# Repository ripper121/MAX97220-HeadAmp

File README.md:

# MAX97220-HeadAmp
HeadAmp-MAX97220A

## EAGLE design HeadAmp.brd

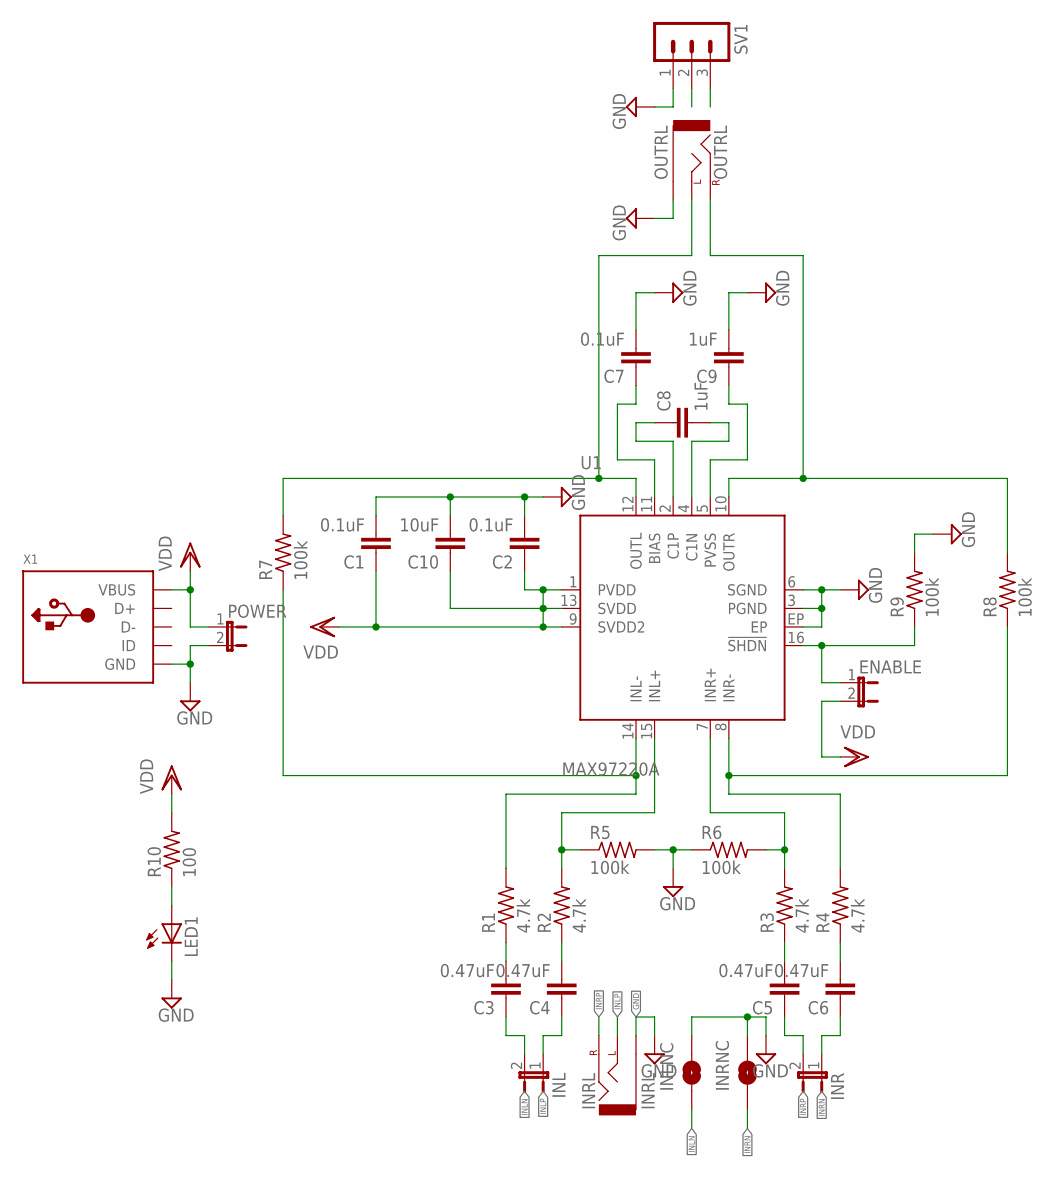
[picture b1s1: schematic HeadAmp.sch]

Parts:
C1, C2, C7: 0.1uF; C0603
C3, C4, C5, C6: 0.47uF; C0603
C8, C9: 1uF; C0603
C10: 10uF; C0603
ENABLE: JP1E; JP1
INL: JP1E; JP1
INLNC: SOLDERJUMPERNO; SJ_2S-NO
INR: JP1E; JP1
INRL: INRL; AUDIO-JACK-3.5MM-SMD
INRNC: SOLDERJUMPERNO; SJ_2S-NO
LED1: LEDCHIP-LED0805; CHIP-LED0805
OUTRL: OUTRL; AUDIO-JACK-3.5MM-SMD
POWER: JP1E; JP1
R1, R2, R3, R4: 4.7k; R0603
R5, R6, R7, R8, R9: 100k; R0603
R10: 100; R0603
SV1: MA03-1
U1: MAX97220A; TQFN16
X1: USB_MICRO_20329_V2; 4UCONN_20329_V2

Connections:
GND: C1.2, C2.2, C7.2, C9.2, C10.2, INLNC.2, INRL.5, INRNC.2, LED1.C, OUTRL.5, POWER.2, R5.2, R6.1, R9.2, SV1.1, U1.3 (PGND), U1.6 (SGND), U1.EP, X1.BASE@1 (GND), X1.BASE@2 (GND), X1.GND, X1.SPRT@1 (GND), X1.SPRT@2 (GND), X1.SPRT@3 (GND), X1.SPRT@4 (GND)
INLN: C3.1, INL.2, INLNC.1
INLP: C4.1, INL.1, INRL.4
INRN: C6.1, INR.1, INRNC.1
INRP: C5.1, INR.2, INRL.1
LOUT: OUTRL.4, R7.2, SV1.2, U1.12 (OUTL)
unnamed: C8.1, U1.2 (C1P)
unnamed: C8.2, U1.4 (C1N)
unnamed: C9.1, U1.5 (PVSS)
unnamed: C7.1, U1.11 (BIAS)
unnamed: ENABLE.1, R9.1, U1.16 (!SHDN)
unnamed: LED1.A, R10.1
unnamed: C3.2, R1.1
unnamed: C4.2, R2.1
unnamed: C5.2, R3.1
unnamed: C6.2, R4.1
unnamed: R2.2, R5.1, U1.15 (INL+)
unnamed: R3.2, R6.2, U1.7 (INR+)
unnamed: R1.2, R7.1, U1.14 (INL-)
unnamed: R4.2, R8.1, U1.8 (INR-)
ROUT: OUTRL.1, R8.2, SV1.3, U1.10 (OUTR)
VDD: C1.1, C2.1, C10.1, ENABLE.2, POWER.1, R10.2, U1.1 (PVDD), U1.9 (SVDD2), U1.13 (SVDD), X1.VBUS

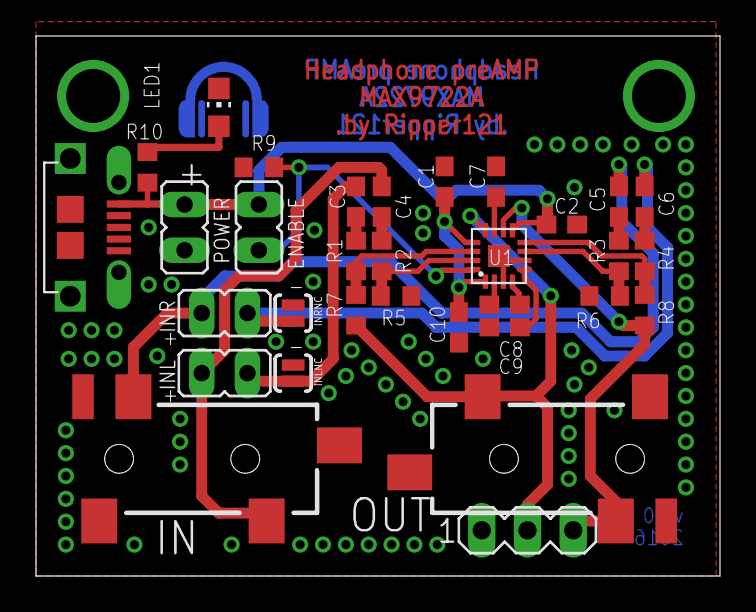
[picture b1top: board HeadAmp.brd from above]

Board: 2 copper layers, 38.0 x 30.0 mm, 32 parts (0 on the bottom side), 22 nets.

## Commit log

2016-11-11 FirstVersion
2016-11-11 PDF files
2016-11-21 Changed Gain to Max

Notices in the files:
parts and their libraries:
SparkFun-Connectors: Licensing: Creative Commons ShareAlike 4.0 International - https://creativecommons.org/licenses/by-sa/4.0
